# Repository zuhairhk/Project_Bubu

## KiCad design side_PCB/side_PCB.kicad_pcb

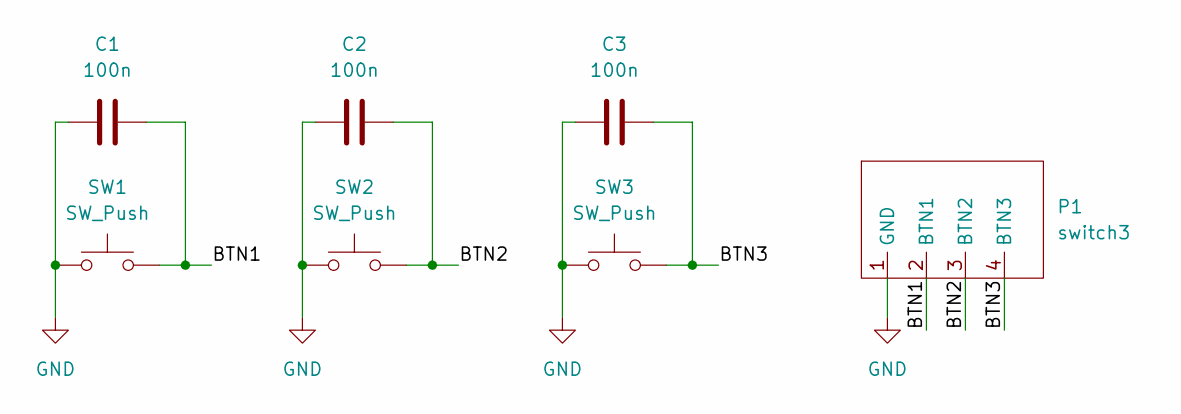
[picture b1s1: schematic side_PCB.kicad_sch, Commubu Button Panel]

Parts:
C1, C2, C3: 100n; C_0402_1005Metric_Pad0.74x0.62mm_HandSolder
P1: switch3; Buttons_header
SW1, SW2, SW3: SW_Push; SW_PUSH_6mm

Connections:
/BTN1: C1.2, P1.2 (BTN1), SW1.2
/BTN2: C2.2, P1.3 (BTN2), SW2.2
/BTN3: C3.2, P1.4 (BTN3), SW3.2
GND: C1.1, C2.1, C3.1, P1.1 (GND), SW1.1, SW2.1, SW3.1

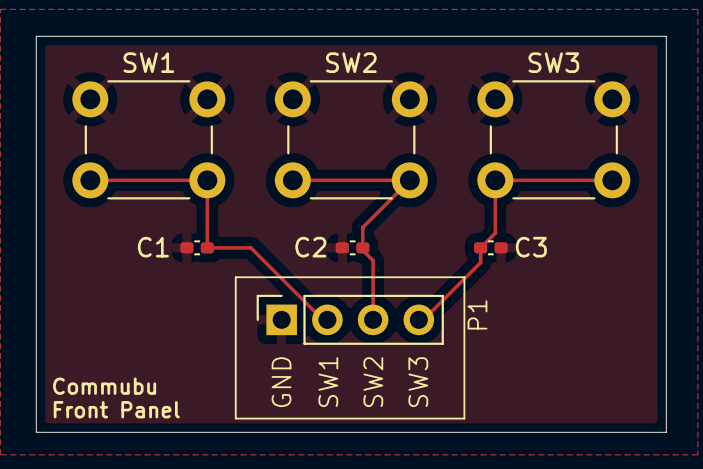
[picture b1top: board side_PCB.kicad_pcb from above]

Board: 4 copper layers, 35.0 x 22.0 mm, 7 parts (0 on the bottom side), 4 nets.

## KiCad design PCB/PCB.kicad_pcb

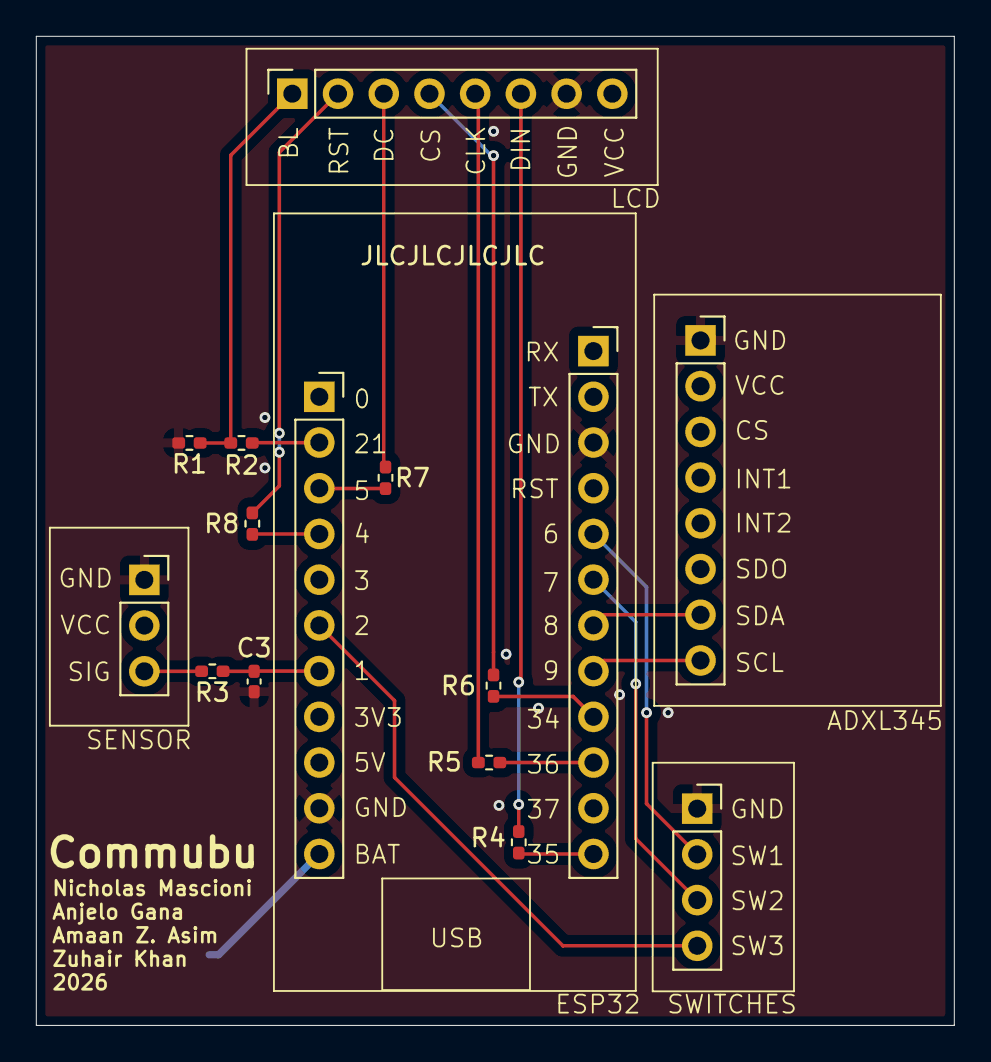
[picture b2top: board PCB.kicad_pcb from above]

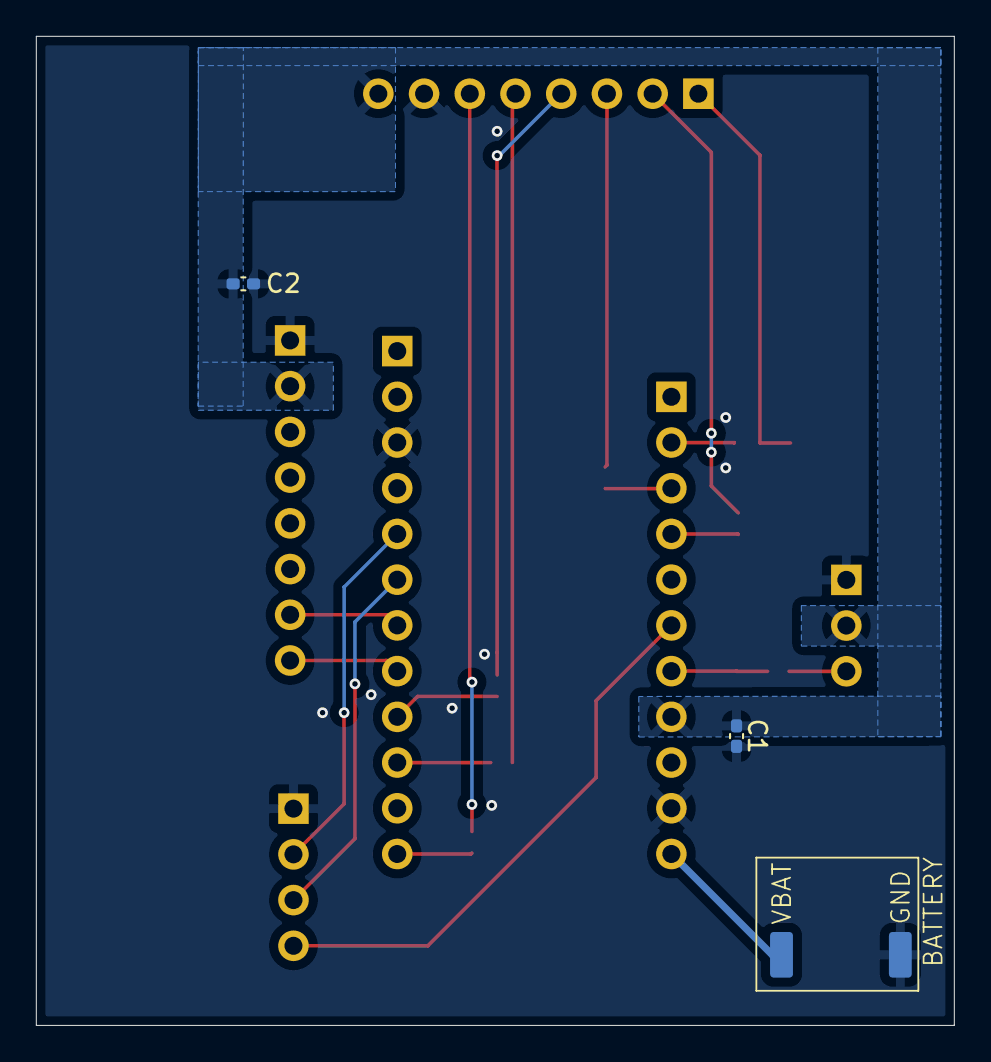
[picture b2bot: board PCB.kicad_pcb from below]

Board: 4 copper layers, 51.0 x 55.0 mm, 17 parts (3 on the bottom side), 22 nets.

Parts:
ADXL345: ADXL345; ADXL345_header
BATTERY: LiPO Pads; Battery_pads
C1, C2: 10u; C_0402_1005Metric_Pad0.74x0.62mm_HandSolder
C3: 0.1u; C_0402_1005Metric_Pad0.74x0.62mm_HandSolder
ESP32: TinyS3_Symbol; TinyS3D_headers
LCD: ST7789V; LCD_header
R1: 100k; R_0402_1005Metric_Pad0.72x0.64mm_HandSolder
R2, R4, R5, R6, R7, R8: 220; R_0402_1005Metric_Pad0.72x0.64mm_HandSolder
R3: 1k; R_0402_1005Metric_Pad0.72x0.64mm_HandSolder
SENSOR: SEN-11574; Heart_headers
SWITCHES: switch3; Buttons_header

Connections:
+3V3: ADXL345.2 (VCC), C1.1, C2.1, ESP32.4 (3V3), LCD.8 (VCC), SENSOR.2 (V+)
+BATT: BATTERY.1 (VBAT), ESP32.1 (VBAT)
/BL: ESP32.10 (IO21), R2.1
/BTN1: ESP32.16 (IO6), SWITCHES.2 (BTN1)
/BTN2: ESP32.17 (IO7), SWITCHES.3 (BTN2)
/BTN3: ESP32.6 (IO2), SWITCHES.4 (BTN3)
/CLK: ESP32.21 (IO36), R5.1
/CS: ESP32.20 (IO34), R6.1
/DC: ESP32.9 (IO5), R7.1
/DIN: ESP32.23 (IO35), R4.1
/FILTER_IN: R3.2, SENSOR.3 (SIGNAL)
/FILTER_OUT: C3.1, ESP32.5 (IO1), R3.1
/RST: ESP32.8 (IO4), R8.1
/SCL: ADXL345.8 (SCL), ESP32.19 (IO9)
/SDA: ADXL345.7 (SDA), ESP32.18 (IO8)
GND: ADXL345.1 (GND), BATTERY.2 (GND), C1.2, C2.2, C3.2, ESP32.2 (GND), ESP32.14 (GND), LCD.7 (GND), R1.2, SENSOR.1 (GND), SWITCHES.1 (GND)
unnamed: LCD.1 (BL), R1.1, R2.2
unnamed: LCD.5 (CLK), R5.2
unnamed: LCD.4 (CS), R6.2
unnamed: LCD.3 (DC), R7.2
unnamed: LCD.6 (DIN), R4.2
unnamed: LCD.2 (RST), R8.2

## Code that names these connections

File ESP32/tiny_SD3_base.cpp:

#include <Arduino.h>
#include <Wire.h>
#include <SPI.h>
#include <Adafruit_GFX.h>
#include <Adafruit_ST7789.h>
#include "driver/rtc_io.h"   // RTC GPIO helpers (wake pins)
#include "driver/gpio.h"     // GPIO hold for deep sleep (backlight)

// ---- TFT (ST7789) ----
#define TFT_MOSI 35   // SPI MO
#define TFT_SCLK 36   // SPI SCK
#define TFT_CS   34
#define TFT_DC   5
#define TFT_RST  4
#define TFT_BL   21   // BL enable (HIGH=on, LOW=off)

// ---- I2C ----
#define I2C_SDA  8
#define I2C_SCL  9

// ---- Heart sensor (analog) ----
#define HR_ADC   1    // A0 / GPIO1

// ---- Buttons (active-low) ----
#define BTN1     6
#define BTN2     7
#define BTN3     2

// ---------------- Debounce + sleep timing ----------------
static const uint32_t DEBOUNCE_MS   = 35;     // typical 20–60ms
static const uint32_t SLEEP_IDLE_MS = 2000;   // idle time before sleeping
static const uint32_t RTC_QUIET_MS  = 800;    // must be HIGH this long before sleeping

struct DebouncedButton {
  uint8_t pin;
  bool stableState;          // debounced state (HIGH idle, LOW pressed)
  bool lastStableState;      // previous debounced state
  bool lastRaw;              // last raw read
  uint32_t lastChangeMs;     // when raw last changed

  void begin(uint8_t p) {
    pin = p;
    pinMode(pin, INPUT_PULLUP);
    bool raw = digitalRead(pin);
    stableState = raw;
    lastStableState = raw;
    lastRaw = raw;
    lastChangeMs = millis();
  }

  void update() {
    bool raw = digitalRead(pin);

    if (raw != lastRaw) {
      lastRaw = raw;
      lastChangeMs = millis();
    }

    if ((millis() - lastChangeMs) >= DEBOUNCE_MS) {
      lastStableState = stableState;
      stableState = raw;
    }
  }

  bool fell() const { return (lastStableState == HIGH && stableState == LOW); }
  bool pressed() const { return (stableState == LOW); }
};

DebouncedButton b1, b2, b3;

// Create display object
Adafruit_ST7789 tft = Adafruit_ST7789(&SPI, TFT_CS, TFT_DC, TFT_RST);

static void screenOff() { digitalWrite(TFT_BL, LOW); }
static void screenOn()  { digitalWrite(TFT_BL, HIGH); }

static void initTFT() {
  // Keep BL OFF during init to avoid visible flicker
  screenOff();

  // Put control pins in safe states early
  pinMode(TFT_CS, OUTPUT);  digitalWrite(TFT_CS, HIGH); // deselect TFT
  pinMode(TFT_DC, OUTPUT);  digitalWrite(TFT_DC, HIGH);
  pinMode(TFT_RST, OUTPUT); digitalWrite(TFT_RST, HIGH);

  // Init SPI
  SPI.begin(TFT_SCLK, -1, TFT_MOSI, TFT_CS);

  // Init ST7789
  tft.init(240, 320);
  tft.setRotation(1);
  // NOTE: series resistors on SCLK/MOSI/DC/CS/RST + lower SPI speed reduce wake flicker/back-power artifacts.
  tft.setSPISpeed(20000000);  // 20 MHz

  // Clear BEFORE turning on backlight
  tft.fillScreen(ST77XX_BLACK);

  // Now turn on the backlight
  screenOn();
  delay(5);
}

static void drawUI(const char* title, int hrRaw, const char* wakeStr) {
  tft.fillScreen(ST77XX_BLACK);

  tft.setTextWrap(false);
  tft.setTextColor(ST77XX_WHITE);
  tft.setTextSize(2);

  tft.setCursor(10, 10);
  tft.print(title);

  tft.setTextSize(1);
  tft.setCursor(10, 50);
  tft.print("Wake: ");
  tft.print(wakeStr);

  tft.setTextSize(2);
  tft.setCursor(10, 90);
  tft.print("HR ADC: ");
  tft.print(hrRaw);

  tft.setTextSize(1);
  tft.setCursor(10, 140);
  tft.print("BTN1/2/3 to stay awake.");
  tft.setCursor(10, 160);
  tft.print("Idle -> deep sleep.");
}

static const char* wakeCauseToStr(esp_sleep_wakeup_cause_t cause) {
  switch (cause) {
    case ESP_SLEEP_WAKEUP_EXT1: return "EXT1 (buttons)";
    case ESP_SLEEP_WAKEUP_TIMER: return "TIMER";
    case ESP_SLEEP_WAKEUP_UNDEFINED: return "POWERON/RESET";
    default: return "OTHER";
  }
}

// -------- EXT1 wake diagnostics --------
static void printExt1Status() {
  uint64_t st = esp_sleep_get_ext1_wakeup_status();
  if (st == 0) {
    Serial.println("EXT1 status: 0 (no pin reported)");
    return;
  }
  Serial.print("EXT1 wake status mask: 0x");
  Serial.println((uint32_t)st, HEX);

  if (st & (1ULL << BTN1)) Serial.println(" -> BTN1 was LOW");
  if (st & (1ULL << BTN2)) Serial.println(" -> BTN2 was LOW");
  if (st & (1ULL << BTN3)) Serial.println(" -> BTN3 was LOW");
}

// -------- RTC wake-pin setup --------
static void configureRtcWakePins() {
  const gpio_num_t wakePins[] = {
    (gpio_num_t)BTN1,
    (gpio_num_t)BTN2,
    (gpio_num_t)BTN3
  };

  for (auto p : wakePins) {
    rtc_gpio_deinit(p);
    rtc_gpio_init(p);
    rtc_gpio_set_direction(p, RTC_GPIO_MODE_INPUT_ONLY);
    rtc_gpio_pullup_en(p);      // keep HIGH when unpressed
    rtc_gpio_pulldown_dis(p);
    rtc_gpio_hold_en(p);        // keep config during deep sleep
  }
}

// Require all RTC button levels HIGH continuously for ms
static bool rtcButtonsAllHighFor(uint32_t ms) {
  uint32_t start = millis();
  while (millis() - start < ms) {
    int r1 = rtc_gpio_get_level((gpio_num_t)BTN1);
    int r2 = rtc_gpio_get_level((gpio_num_t)BTN2);
    int r3 = rtc_gpio_get_level((gpio_num_t)BTN3);

    if (r1 == 0 || r2 == 0 || r3 == 0) {
      Serial.print("RTC levels not all HIGH: BTN1=");
      Serial.print(r1);
      Serial.print(" BTN2=");
      Serial.print(r2);
      Serial.print(" BTN3=");
      Serial.println(r3);
      return false;
    }
    delay(5);
  }
  return true;
}

static void enterDeepSleep() {
  // 1) Turn backlight off
  screenOff();
  delay(5);

  // 2) HOLD backlight LOW through deep sleep (prevents it popping back on)
  pinMode(TFT_BL, OUTPUT);
  digitalWrite(TFT_BL, LOW);
  gpio_hold_en((gpio_num_t)TFT_BL);
  gpio_deep_sleep_hold_en();

  // 3) Hi-Z TFT pins to reduce back-power paths
  pinMode(TFT_CS,   INPUT);
  pinMode(TFT_DC,   INPUT);
  pinMode(TFT_RST,  INPUT);
  pinMode(TFT_MOSI, INPUT);
  pinMode(TFT_SCLK, INPUT);

  // 4) Clear wake sources and configure RTC wake pins
  esp_sleep_disable_wakeup_source(ESP_SLEEP_WAKEUP_ALL);
  configureRtcWakePins();
  delay(20);

  // 5) Quiet window: ALL wake pins must be HIGH or we would wake instantly
  if (!rtcButtonsAllHighFor(RTC_QUIET_MS)) {
    Serial.println("Sleep aborted: wake pin LOW/noisy (would wake instantly).");

    // Release holds so you can continue running normally
    gpio_deep_sleep_hold_dis();
    gpio_hold_dis((gpio_num_t)TFT_BL);
    screenOn();
    return;
  }

  // 6) EXT1 wake on ANY LOW
  const uint64_t wakeMask =
      (1ULL << BTN1) |
      (1ULL << BTN2) |
      (1ULL << BTN3);

  esp_sleep_enable_ext1_wakeup(wakeMask, ESP_EXT1_WAKEUP_ANY_LOW);

  Serial.println("Entering deep sleep now.");
  Serial.flush();
  esp_deep_sleep_start();
}

void setup() {
  Serial.begin(115200);
  delay(50);

  // Keep SPI pins quiet on boot to reduce flicker
  pinMode(TFT_BL, OUTPUT);  digitalWrite(TFT_BL, LOW);
  pinMode(TFT_CS, OUTPUT);  digitalWrite(TFT_CS, HIGH);
  pinMode(TFT_DC, OUTPUT);  digitalWrite(TFT_DC, HIGH);
  pinMode(TFT_RST, OUTPUT); digitalWrite(TFT_RST, HIGH);
  pinMode(TFT_MOSI, OUTPUT); digitalWrite(TFT_MOSI, LOW);
  pinMode(TFT_SCLK, OUTPUT); digitalWrite(TFT_SCLK, LOW);


  // IMPORTANT: release any deep-sleep holds from the previous sleep cycle
  gpio_deep_sleep_hold_dis();
  gpio_hold_dis((gpio_num_t)TFT_BL);

  // Buttons (active-low) + debouncers
  b1.begin(BTN1);
  b2.begin(BTN2);
  b3.begin(BTN3);

  // BL control
  pinMode(TFT_BL, OUTPUT);
  screenOff(); // start OFF to avoid boot flash

  // I2C init
  Wire.begin(I2C_SDA, I2C_SCL);

  // ADC setup
  analogReadResolution(12);
  analogSetPinAttenuation(HR_ADC, ADC_11db);

  // TFT init
  initTFT();

  // Wake reason
  esp_sleep_wakeup_cause_t cause = esp_sleep_get_wakeup_cause();
  const char* causeStr = wakeCauseToStr(cause);

  Serial.print("Wake cause: ");
  Serial.println(causeStr);
  if (cause == ESP_SLEEP_WAKEUP_EXT1) {
    printExt1Status();
  }

  // Read HR once for demo
  int hrRaw = analogRead(HR_ADC);
  drawUI("TinyS3[D] Watch UI", hrRaw, causeStr);
}

void loop() {
  static uint32_t lastActivity = millis();

  // Update debouncers
  b1.update();
  b2.update();
  b3.update();

  // Activity on debounced press edge
  if (b1.fell() || b2.fell() || b3.fell()) {
    lastActivity = millis();
  }

  // Update HR reading periodically while awake
  static uint32_t lastUpdate = 0;
  if (millis() - lastUpdate > 250) {
    lastUpdate = millis();
    int hrRaw = analogRead(HR_ADC);

    tft.fillRect(10, 90, 220, 30, ST77XX_BLACK);
    tft.setCursor(10, 90);
    tft.setTextSize(2);
    tft.setTextColor(ST77XX_WHITE);
    tft.print("HR ADC: ");
    tft.print(hrRaw);
  }

  // Sleep after idle
  if (millis() - lastActivity > SLEEP_IDLE_MS) {
    Serial.println("Sleeping...");
    enterDeepSleep();
    lastActivity = millis(); // if aborted, avoid spamming
  }

  delay(10);
}

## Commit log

2025-10-16 Init of Django backend
2025-10-27 Importing GO Transit API
2025-10-31 MCR-3 Update Changes
2025-11-05 Initial ESP32 tests
2025-11-06 Added ESP32 pinout to README
2025-11-06 OLED example
2025-11-07 Flatten folder structure
2025-11-07 Updated gitignore
2025-11-07 Testing YRT Protocol Buffer file
2025-11-13 Fix windows repo
2025-11-22 Big screen is working and docs updated
2025-11-28 WSL Push
2026-01-11 Static face with real time accelerometer updates
2026-01-11 Custom face on UI with python script to generate bitmap
2026-01-16 Added requirements.txt
2026-01-18 react native app created
2026-01-19 removed top header from app
2026-01-22 SUUUUPER rough layout of the tabs we want for the app
2026-01-22 renaming mobile dir
2026-01-22 Pixel Editor V1
2026-01-22 Steps Count v1
2026-01-22 Reworked backend to FastAPI
2026-01-23 Normalizing GO transit provider
2026-02-02 Updated custom face generator for new MCU
2026-02-02 New base code for new MCU with button debouncing
2026-02-02 Initial PCB with new MCU
2026-02-04 api health route
2026-02-04 SSL tweaks for go api
2026-02-09 BLE Tx and Rx working with nRF App
2026-02-12 Custom footprints and sch update with footprints
2026-02-12 Sch rev3, fixed pin numbers to match footprints
2026-02-12 PCB ready for layout
2026-02-13 Added USBC measurement to footprint
2026-02-13 Step counter updated
2026-02-14 Floorplan, routing WIP
2026-02-14 Floorplan done, routing WIP
2026-02-15 PCB routed and DRC clean
2026-02-15 Added battery soldering pads
2026-03-09 Hi Mascioli
2026-03-09 Remove hello.py
2026-03-09 Heart rate mapped and debug mode function
2026-03-09 Most recent PCB revisions, after fixing header width
2026-03-09 Animation
2026-03-09 button PCB
2026-03-09 Added music bar with placeholder
2026-03-09 Pre app BLE functions with nRF
2026-03-09 Updated cpp
2026-03-09 Backend updates with ml model training
2026-03-09 BLE with animations from Anjelo
2026-03-09 More emotions
2026-03-09 updated with buttons
2026-03-09 radial menu added
2026-03-09 Mobile app w ble connectivity
2026-03-09 shminglus binglus
2026-03-09 rm old mobile app
2026-03-09 Battery indicator added to UI
2026-03-09 WE DID IT WE DID IT
2026-03-09 Button triggered animations
2026-03-09 read and write to esp32
2026-03-09 Backend ML model input
2026-03-09 Working heart rate and animations
2026-03-10 Fixed BLE TX for heart rate, now transmits an integer (in hex) rather than an ASCII string
2026-03-12 mobile app mods
2026-03-12 Updated basefile
2026-03-13 iOS build and transit update
2026-03-13 Keep pulled model_metadata.json
2026-03-13 Ignore KiCad backup files
2026-03-13 Buttons now switch between music, home, and commute screens, fixed flicker on transition
2026-03-20 Map of BLE UUIDs currently in place
2026-03-23 lottie removal
2026-03-23 fixing biometrics progress bar
2026-03-23 I HATE ANIMATIONS
2026-03-23 fixing app crash on launch
2026-03-24 ml with spotofy integration
2026-03-24 spotify song rec tweaks
2026-03-24 playlist gen tweaks
2026-03-24 spotify login logout for fresh tokens
2026-03-24 token expiry debugging
2026-03-24 auth with all scopes modified
2026-03-24 debugging playlist gen
2026-03-24 retraining model every 10 samples
2026-03-24 homescreen revamp
2026-03-24 homescreen revamp v2
2026-03-24 homescreen revamp minimal
2026-03-24 homescreen revamp minimal v2
2026-03-24 UI tweaks to biometrics page
2026-03-24 UI overhaul
2026-03-24 ngrok update
2026-03-24 callback fix for oauth login
2026-03-24 whitescreen auth session wait fix
2026-03-24 updated line info on transit card
2026-03-24 savestate
2026-03-24 api update
2026-03-24 mobile app ble conn
2026-03-25 front page and ble settings
2026-03-25 ble debugging
2026-03-25 firmware update with 36 bytes compressed to 31
2026-03-25 firmware ble debugging
2026-03-25 app ble debugging
2026-03-25 api endpoint update
2026-03-25 spotify api tweaks
2026-03-25 debouncedbutton struct modified for current song playing
2026-03-25 adding now playing feature to app
2026-03-25 added now playing
2026-03-25 hw sw comm
2026-03-25 music page on hardware
2026-03-25 ML model logic tweaks
2026-03-25 playlist recc logic upgrades
2026-03-25 ml data dump
2026-03-28 TEST ANIMATIONS HAVE BEEN LOCKED IN
2026-04-03 matchafication version 1 has been complete
2026-04-04 Fixed API endpoint to deb server
2026-04-04 Fixed API endpoint avec deb server
2026-04-05 mood anim card added
2026-04-05 face anims added, in progress of adding them to app
2026-04-05 face animations completely added successfully
2026-04-05 ble debug menu commented out, changed button layout in playlist
2026-04-05 made menu open up more smoothly
2026-04-05 commubu app icon and splash image added
2026-04-05 app is complete
